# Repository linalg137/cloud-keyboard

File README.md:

<ZINE>

  The cloud keyboard is a simple cloud-shaped 3x3 keyboard designed using KiCAD and Onshape. It connects with a USB, and runs a simple micropython code that prints a designated number on the coding shell for each key when pressed.

## ***Inspiration~***
I made this keyboard because I wanted a to build a personalized cute keyboard completely from scratch. It was my first ever PCB I ever designed, and it helped me learn a LOT. 

## ***Full Instructions~***

**getting the pcb**
1. go to https://jlcpcb.com/. click "get instant quote".
2. download the gerber zip file from the pcb folder and upload it.
3. you can change the color of the PCB if you'd like, but keep all the other settings the same.
4. order your PCB by following the steps on the website.

**getting the parts**
1. To find all the suitable parts needed for this pcb, open the BOM file. This lists all the necessary parts needed for the PCB-- you'll see several links leading to product pages.

**printing the case**
1. download the STL files, or go open this onshape link: https://cad.onshape.com/documents/30ca1b2b31257d2650154877/w/6a6ce5b2935f39e9888c6e90/e/9cf32ad964649424d66e1c2f?renderMode=0&uiState=6a1fb2345d12723005a9a689.
2. follow the directions on your own 3D printer's manufacturer's website/app to upload the STL files in and print them. support for the prints are not neeeded, as long as you have the models sitting on the correct side.

**soldering and putting everything together**
1. solder the pieces together in their designated spots. You can use the .step file to see how it should look like in the end (the battery cell is optional). Make sure to sandwich the keys together with the top of the case, putting the keys in from the top.
2. After you're done soldering it, plug the ESP32 into your device using a USB-C.
3. Import micropython onto your ESP32 by uploading the ESP32_GENERIC_C3-20260406-v1.28.0.bin into the adafruit webserial bootloader (https://adafruit.github.io/Adafruit_WebSerial_ESPTool/)(to start this, click the "connect" button on the upper right corner. no offset is needed.). 
4. Run keys.py on Thonny after connecting to the ESP32 by selecting the suitable option on the lower left corner.

## ***GALLERY~***
<details>
  <summary>3D model, PCB design, schematic, etc</summary>

</details>

## ***Credits~***
This project used:
- [KiCAD](https://www.kicad.org/) (for PCB design)
- [Onshape](https://www.onshape.com/en/platform) (for case design)

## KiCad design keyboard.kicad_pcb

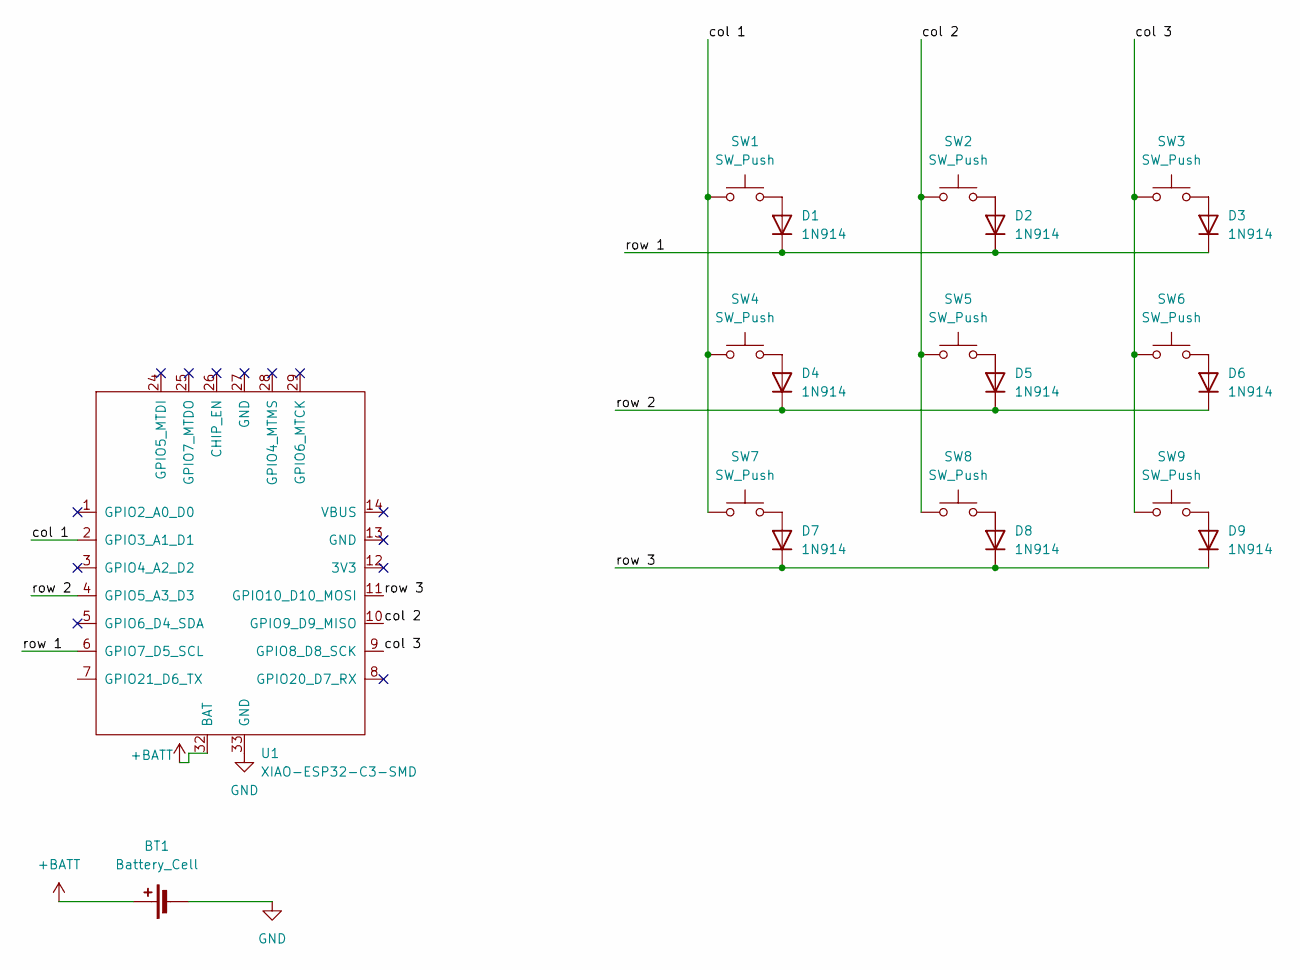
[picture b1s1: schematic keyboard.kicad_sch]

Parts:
BT1: Battery_Cell; PinHeader_1x02_P2.54mm_Vertical
D1, D2, D3, D4, D5, D6, D7, D8, D9: 1N914; D_DO-35_SOD27_P7.62mm_Horizontal
SW1, SW2, SW3, SW4, SW5, SW6, SW7, SW8, SW9: SW_Push; SW_Cherry_MX_1.00u_PCB
U1: XIAO-ESP32-C3-SMD; XIAO-ESP32-C3-DIP-SMD

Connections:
+BATT: BT1.1 (+), U1.32 (BAT)
/col 1: SW1.1, SW4.1, SW7.1, U1.2 (GPIO3_A1_D1)
/col 2: SW2.1, SW5.1, SW8.1, U1.10 (GPIO9_D9_MISO)
/col 3: SW3.1, SW6.1, SW9.1, U1.9 (GPIO8_D8_SCK)
/row 1: D1.1 (K), D2.1 (K), D3.1 (K), U1.6 (GPIO7_D5_SCL)
/row 2: D4.1 (K), D5.1 (K), D6.1 (K), U1.4 (GPIO5_A3_D3)
/row 3: D7.1 (K), D8.1 (K), D9.1 (K), U1.11 (GPIO10_D10_MOSI)
GND: BT1.2 (-), U1.33 (GND)
unnamed: D1.2 (A), SW1.2
unnamed: D2.2 (A), SW2.2
unnamed: D3.2 (A), SW3.2
unnamed: D4.2 (A), SW4.2
unnamed: D5.2 (A), SW5.2
unnamed: D6.2 (A), SW6.2
unnamed: D7.2 (A), SW7.2
unnamed: D8.2 (A), SW8.2
unnamed: D9.2 (A), SW9.2

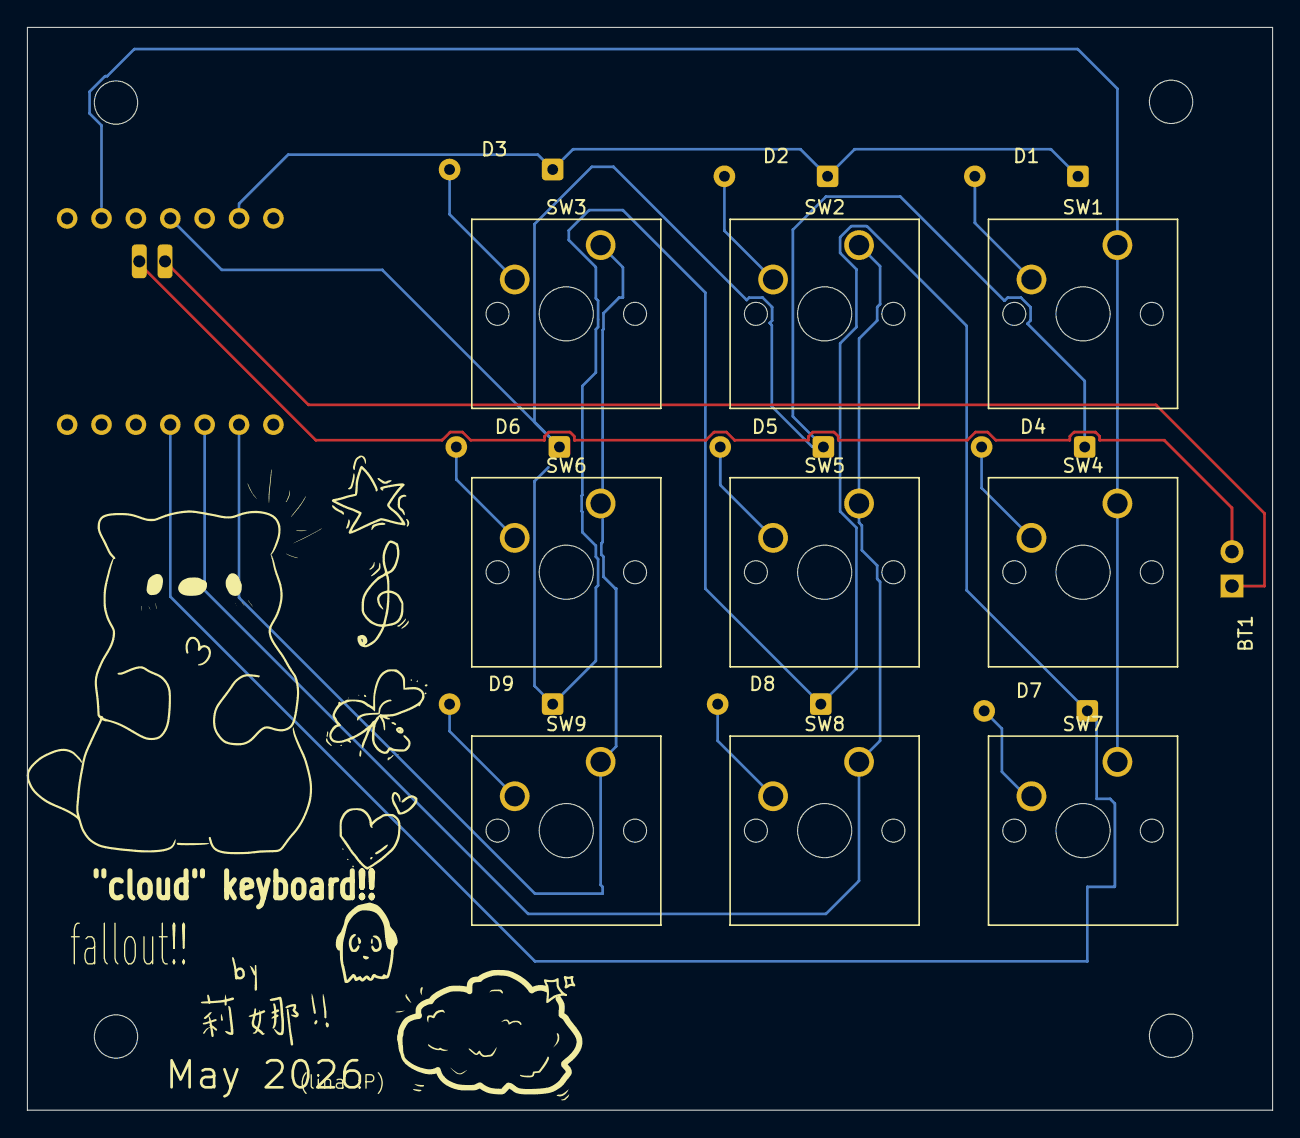
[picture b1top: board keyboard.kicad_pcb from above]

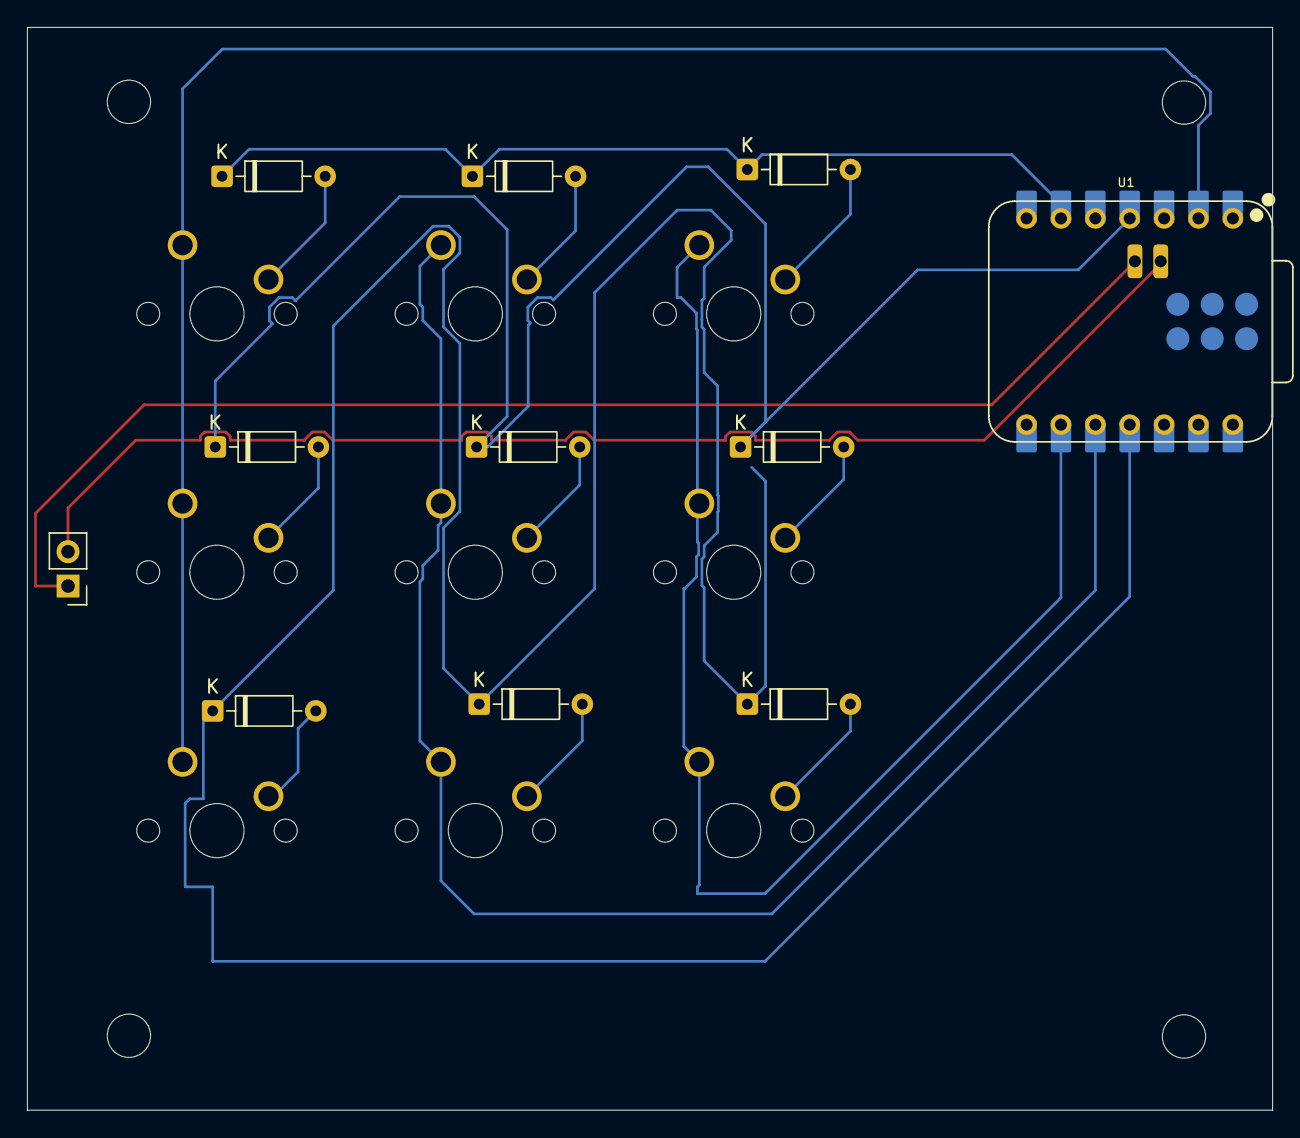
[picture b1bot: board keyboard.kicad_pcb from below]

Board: 2 copper layers, 92.0 x 80.0 mm, 20 parts (11 on the bottom side), 17 nets.

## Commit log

2026-06-02 README.md
2026-06-03 Create e
2026-06-03 Create cb
